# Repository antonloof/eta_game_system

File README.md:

# Eta game system
Playing games on a wall of TLS3001. Driven by a raspberry pi pico

## important docs
https://github.com/FastLED/FastLED/issues/1

Summary:
Manchester encoded data:
1 => 10
0 => 01
Timing is critical, keep constant period!
When sleeping put data low!

Sync frame: "1"*15+"0001"+"0"*11
(111111111111111000100000000000)

Reset frame: "1"*15 + "0100"
(1111111111111110100)

Data frame header: "1"*15 + "0010" 
(1111111111111110010)

Data content: "0"+"x"*12 + "0"+"x"*12 + "0"+"x"*12
where x is the rgb data to send total 39 bits per led
repeat this for all leds in series

The source:
Data communication protocol: 

Gave SDI input signal pin must follow the following definitions:

a. valid input data must be Manchester encoded signal. 

(from high to low transition indicates "1", from low to high Jump indicates "0")

b. During chip power after a synchronization frame must be sent to the chip detection of communication baud rate. Sync frame

Format is: 15'b111111111111111 + 4' b0001 +11' b00000000000, sending synchronization

Frame must be delayed for some time and then send the data frame, so that each chip can be done in order to accurately detect

To the communication baud rate, delay time (us) greater than: Connection chip count ÷ communication baud rate (MHz) × 30

c. several frames in the transmission data, re-send a reset frame, wait 1ms later, send it again with the

Step frames for the chip to eliminate the accumulated error, reset frame format:

15'b111111111111111 +4' b0100

d. data frame format is: 15'b111111111111111 +4' b0010 (header) + first chip

39bit second chip 39bit data + data + ...... + n-th chip 39bit data

e. first chip is first received data chips, chip data format is: 1 'b0 (identification bits) + 12'

bxxxxxxxxxxxx (output port 1 data) + 1'b0 (flag) + 12'bxxxxxxxxxxxx (input

The port 2 data) + 1'b0 (flag) + 12'bxxxxxxxxxxxx (output port 3 data),

x is 1 or the 0

f. data is first sent MSB (most significant bit)

g. SDI input pin in the idle state, must remain low

h. the same frame data transmission process, must be sent contiguously, in the middle, without interruption, transmission frequency can not be Changed.

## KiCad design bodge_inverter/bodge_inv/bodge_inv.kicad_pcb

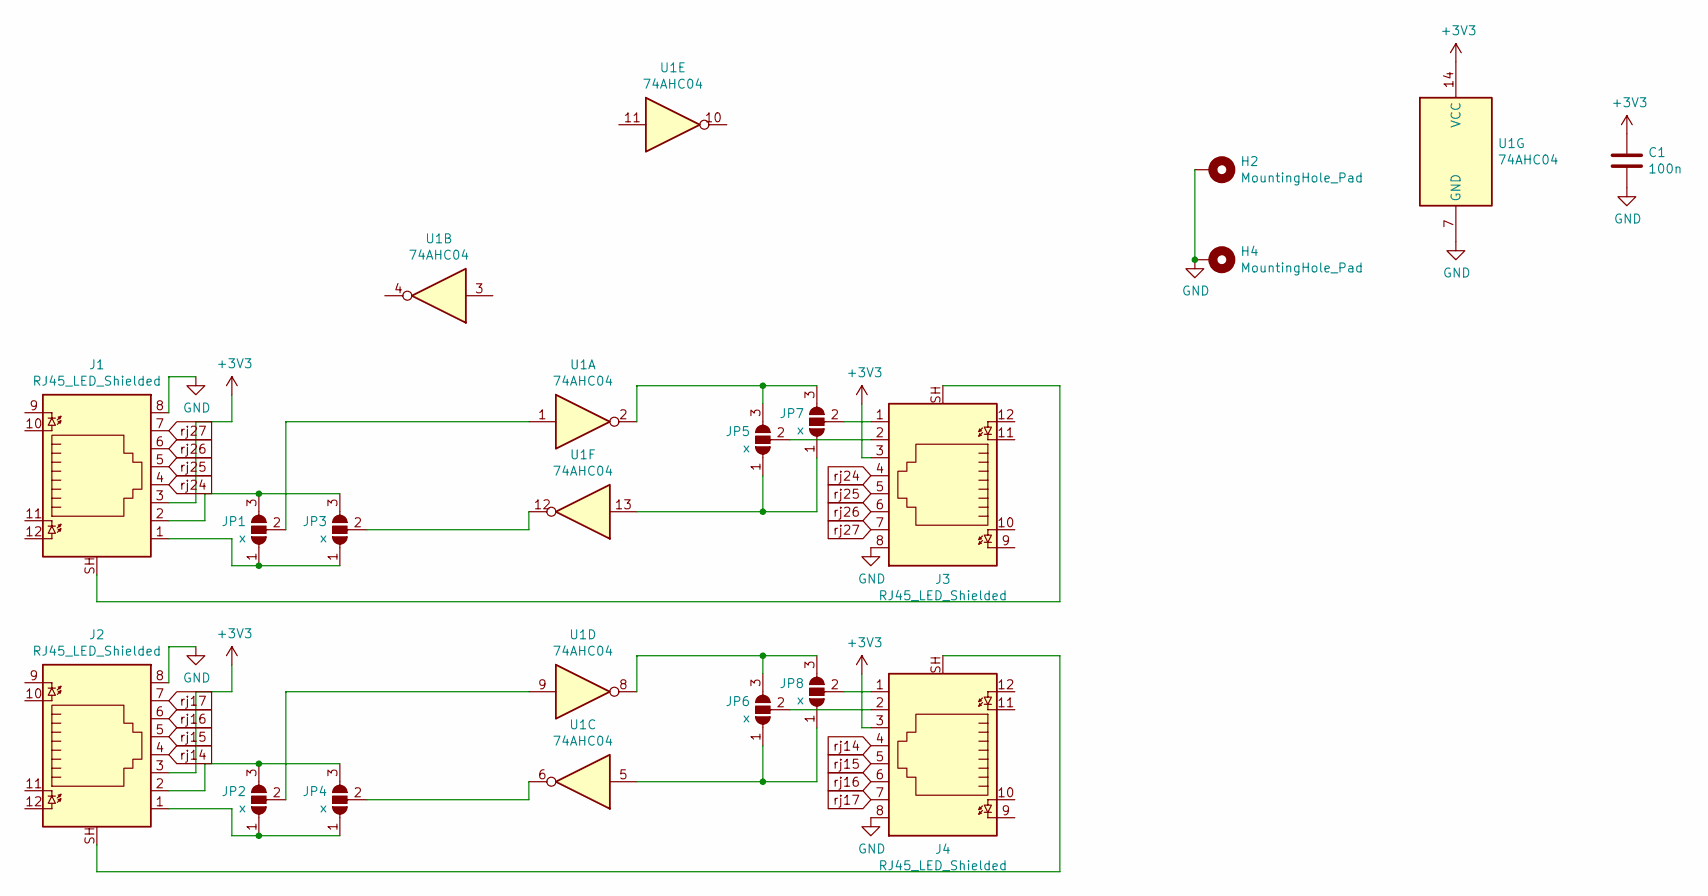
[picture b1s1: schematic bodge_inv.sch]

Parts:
C1: 100n; C_0603_1608Metric_Pad1.05x0.95mm_HandSolder
H2, H4: MountingHole_Pad; MountingHole_3.2mm_M3_Pad
J1, J2, J3, J4: RJ45_LED_Shielded; RJ45_BEL_SS74301-00x_Vertical
JP1, JP2, JP3, JP4, JP5, JP6, JP7, JP8: x; SolderJumper-3_P1.3mm_Open_Pad1.0x1.5mm_NumberLabels
U1: 74AHC04; SOIC-14_3.9x8.7mm_P1.27mm

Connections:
+3V3: C1.1, J1.3, J2.3, J3.3, J4.3, U1.14 (VCC)
GND: C1.2, H2.1, H4.1, J1.8, J2.8, J3.8, J4.8, U1.7 (GND)
unnamed: J1.1, JP1.1 (A), JP3.1 (A)
unnamed: J1.2, JP1.3 (B), JP3.3 (B)
unnamed: J1.SH, J3.SH
unnamed: J2.1, JP2.1 (A), JP4.1 (A)
unnamed: J2.2, JP2.3 (B), JP4.3 (B)
unnamed: J2.SH, J4.SH
unnamed: J3.1, JP7.2 (C)
unnamed: J3.2, JP5.2 (C)
unnamed: J4.1, JP8.2 (C)
unnamed: J4.2, JP6.2 (C)
unnamed: JP1.2 (C), U1.1
unnamed: JP2.2 (C), U1.9
unnamed: JP3.2 (C), U1.12
unnamed: JP4.2 (C), U1.6
unnamed: JP5.1 (A), JP7.1 (A), U1.13
unnamed: JP5.3 (B), JP7.3 (B), U1.2
unnamed: JP6.1 (A), JP8.1 (A), U1.5
unnamed: JP6.3 (B), JP8.3 (B), U1.8
rj14: J2.4, J4.4
rj15: J2.5, J4.5
rj16: J2.6, J4.6
rj17: J2.7, J4.7
rj24: J1.4, J3.4
rj25: J1.5, J3.5
rj26: J1.6, J3.6
rj27: J1.7, J3.7

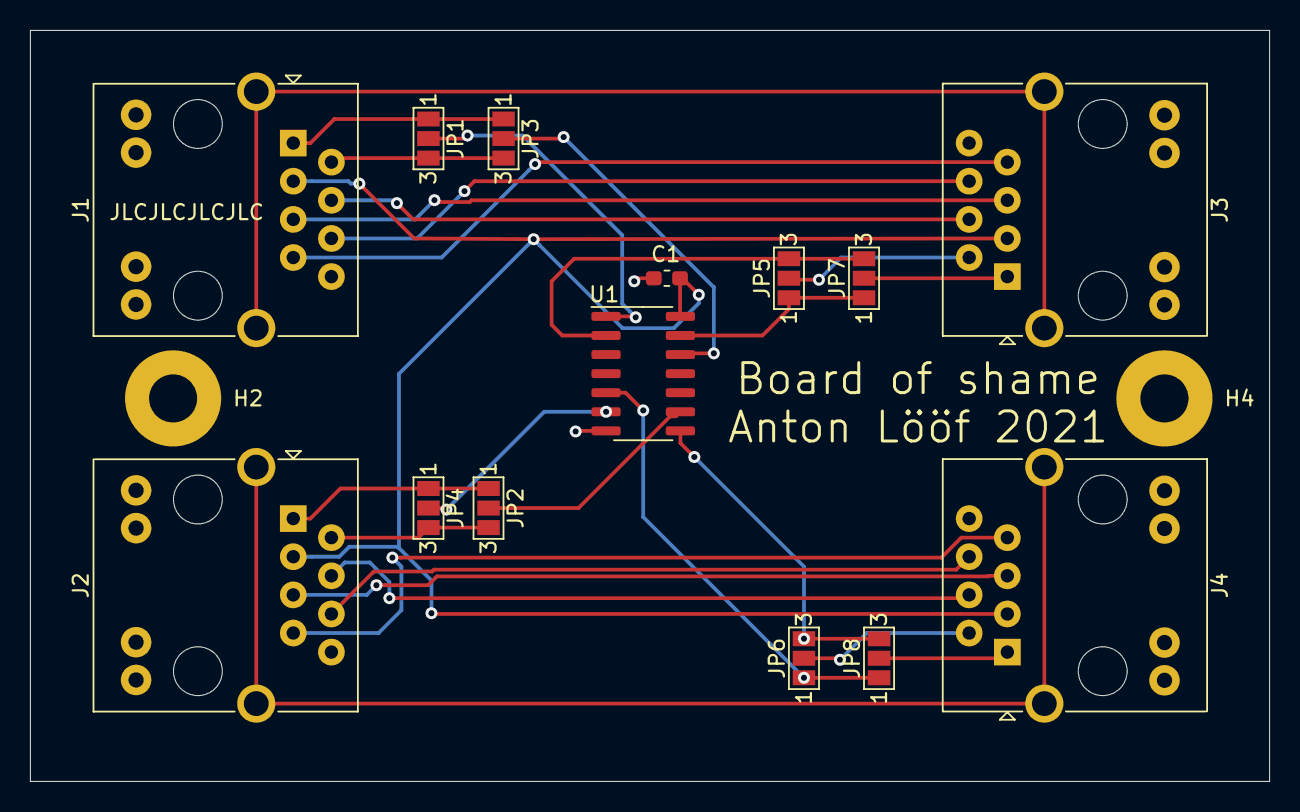
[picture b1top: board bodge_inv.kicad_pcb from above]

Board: 2 copper layers, 82.5 x 50.0 mm, 16 parts (0 on the bottom side), 28 nets.

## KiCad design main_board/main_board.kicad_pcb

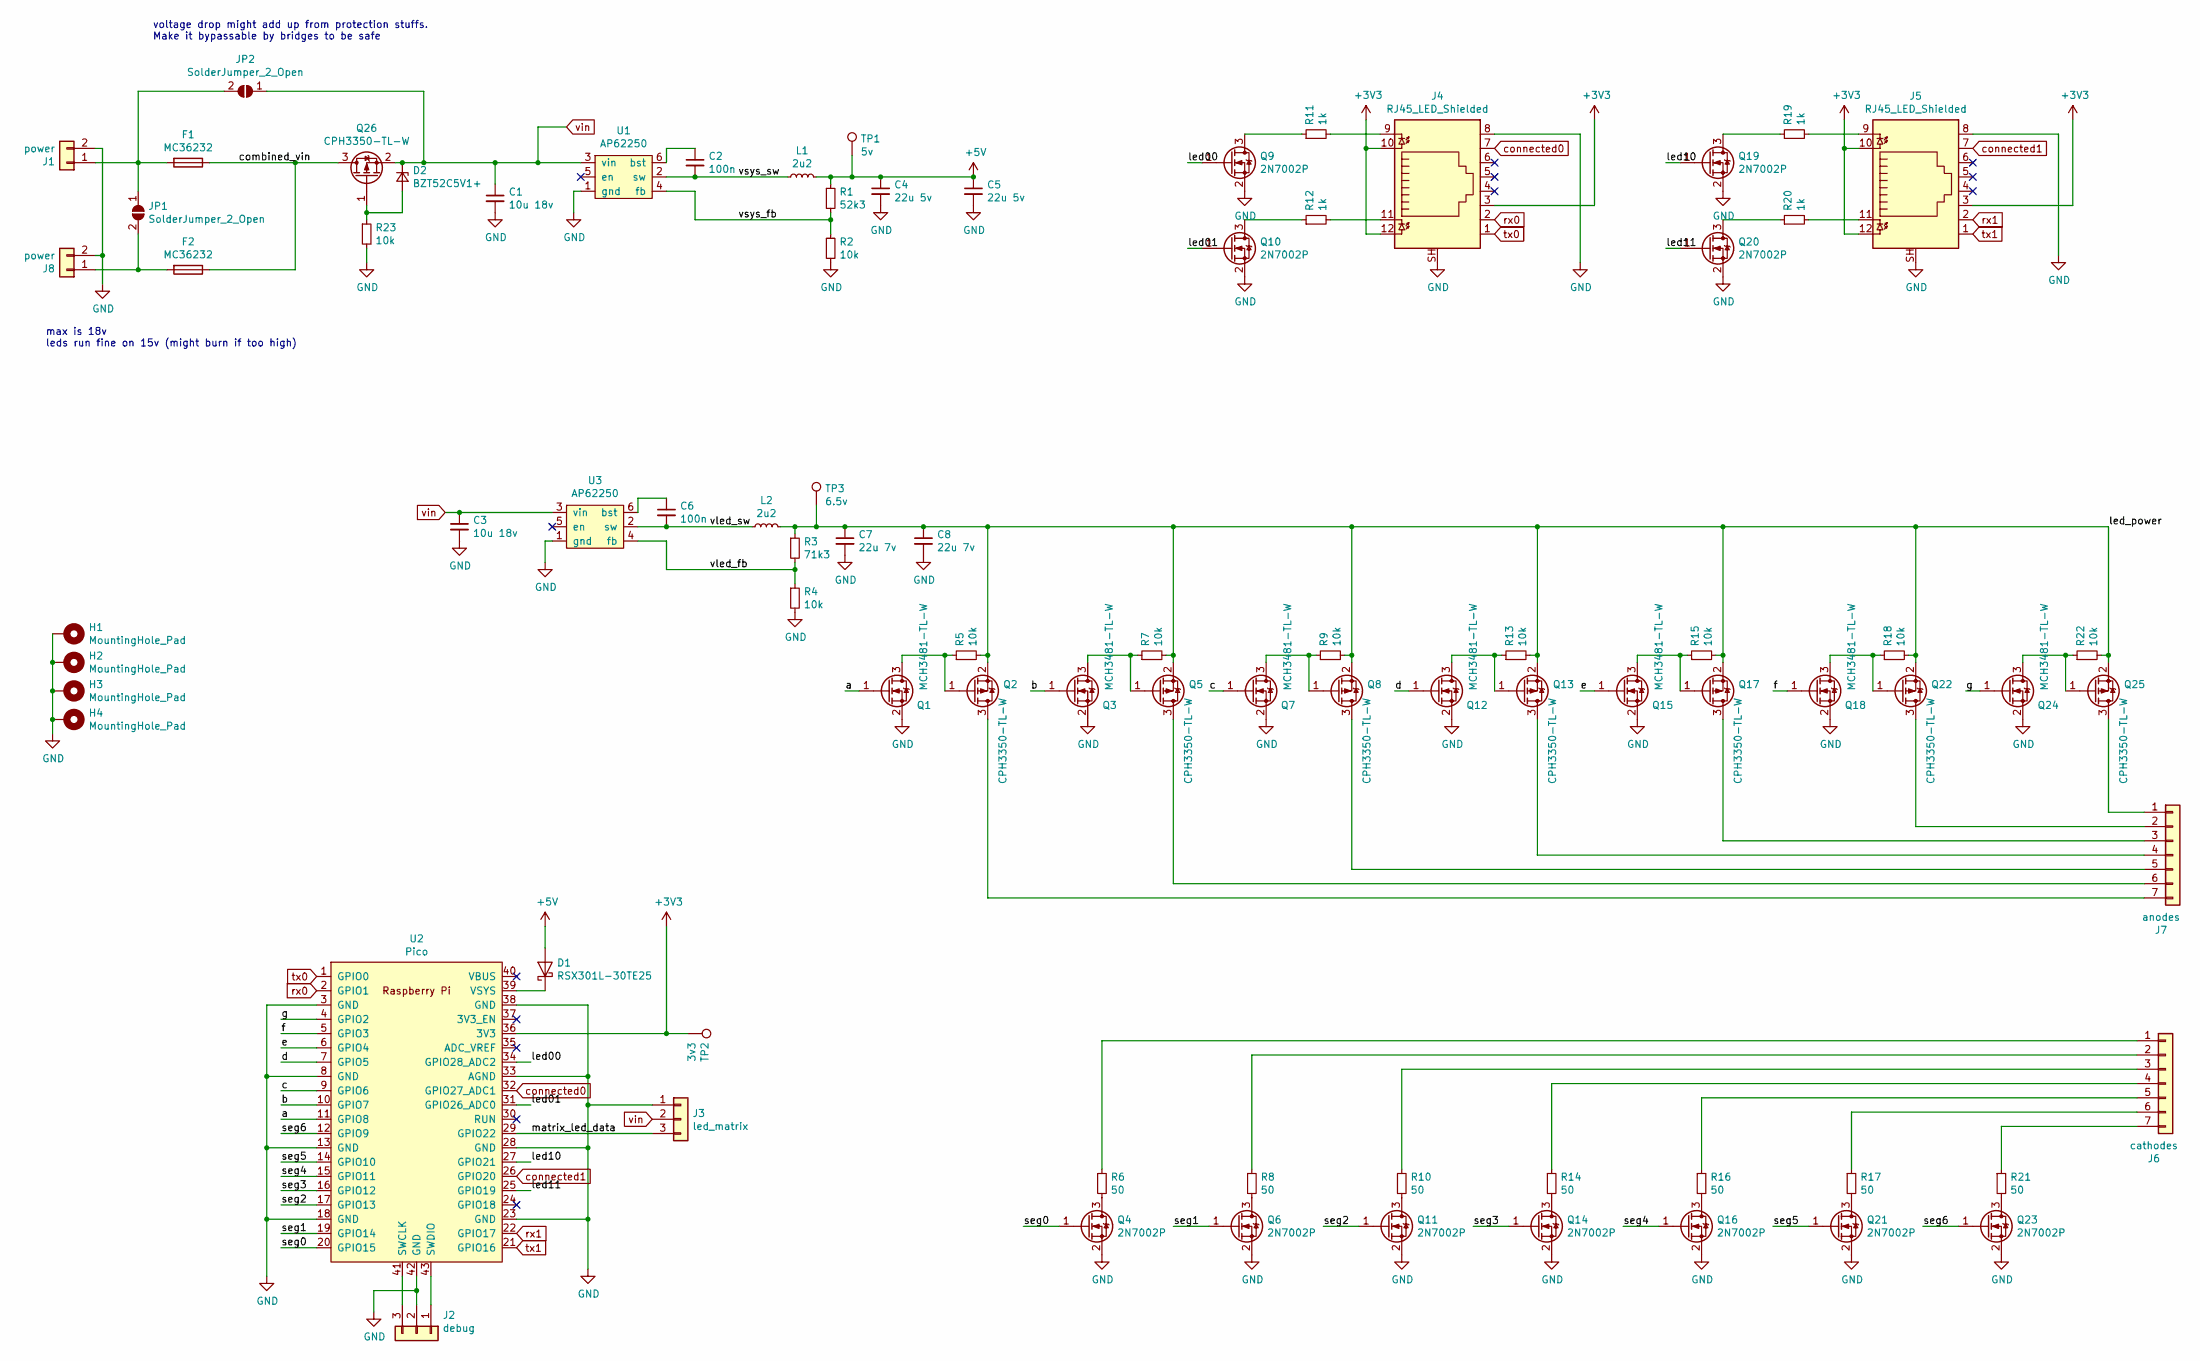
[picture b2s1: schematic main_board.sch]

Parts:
C1, C3: 10u 18v; C_1206_3216Metric
C2, C6: 100n; C_0603_1608Metric_Pad1.08x0.95mm_HandSolder
C4, C5: 22u 5v; C_0603_1608Metric_Pad1.08x0.95mm_HandSolder
C7, C8: 22u 7v; C_0805_2012Metric_Pad1.18x1.45mm_HandSolder
D1: RSX301L-30TE25; smd_diode_sod_106
D2: BZT52C5V1+; D_SOD-123
F1, F2: MC36232; Fuse_1812_4532Metric_Castellated
H1, H2, H3, H4: MountingHole_Pad; MountingHole_3.2mm_M3_Pad_TopBottom
J1, J8: power; TerminalBlock_Phoenix_MKDS-1,5-2_1x02_P5.00mm_Horizontal
J2: debug; PinHeader_1x03_P2.54mm_Vertical
J3: led_matrix; TerminalBlock_Phoenix_MKDS-1,5-3_1x03_P5.00mm_Horizontal
J4, J5: RJ45_LED_Shielded; RJ45_BEL_SS74301-00x_Vertical
J6: cathodes; PinHeader_1x07_P2.54mm_Vertical
J7: anodes; PinHeader_1x07_P2.54mm_Vertical
JP1, JP2: SolderJumper_2_Open; SolderJumper-2_P1.3mm_Open_TrianglePad1.0x1.5mm
L1, L2: 2u2; smd_inductor_0806_2016metric
Q1, Q3, Q7, Q12, Q15, Q18, Q24: MCH3481-TL-W; SOT-323_SC-70_Handsoldering
Q2, Q5, Q8, Q13, Q17, Q22, Q25, Q26: CPH3350-TL-W; SOT-23_Handsoldering
Q4, Q6, Q9, Q10, Q11, Q14, Q16, Q19, Q20, Q21, Q23: 2N7002P; SOT-23_Handsoldering
R1: 52k3; R_0603_1608Metric_Pad0.98x0.95mm_HandSolder
R2, R4, R5, R7, R9, R13, R15, R18, R22, R23: 10k; R_0603_1608Metric_Pad0.98x0.95mm_HandSolder
R3: 71k3; R_0603_1608Metric_Pad0.98x0.95mm_HandSolder
R6, R8, R10, R14, R16, R17, R21: 50; R_0603_1608Metric_Pad0.98x0.95mm_HandSolder
R11, R12, R19, R20: 1k; R_0603_1608Metric_Pad0.98x0.95mm_HandSolder
TP1: 5v; TestPoint_Pad_D1.5mm
TP2: 3v3; TestPoint_Pad_D1.5mm
TP3: 6.5v; TestPoint_Pad_D1.5mm
U1, U3: AP62250; TSOT-23-6
U2: Pico; RPi_Pico_SMD_TH

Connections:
+3V3: J4.3, J4.10, J4.12, J5.3, J5.10, J5.12, TP2.1, U2.36 (3V3)
+5V: C4.1, C5.1, D1.2 (A), L1.2, R1.1, TP1.1
/a: Q1.1 (G), U2.11 (GPIO8)
/b: Q3.1 (G), U2.10 (GPIO7)
/c: Q7.1 (G), U2.9 (GPIO6)
/combined_vin: F1.1, F2.1, Q26.3 (D)
/d: Q12.1 (G), U2.7 (GPIO5)
/e: Q15.1 (G), U2.6 (GPIO4)
/f: Q18.1 (G), U2.5 (GPIO3)
/g: Q24.1 (G), U2.4 (GPIO2)
/led00: Q9.1 (G), U2.34 (GPIO28_ADC2)
/led01: Q10.1 (G), U2.31 (GPIO26_ADC0)
/led10: Q19.1 (G), U2.27 (GPIO21)
/led11: Q20.1 (G), U2.25 (GPIO19)
/led_power: C7.1, C8.1, L2.2, Q2.2 (S), Q5.2 (S), Q8.2 (S), Q13.2 (S), Q17.2 (S), Q22.2 (S), Q25.2 (S), R3.1, R5.2, R7.2, R9.2, R13.2, R15.2, R18.2, R22.2, TP3.1
/matrix_led_data: J3.3, U2.29 (GPIO22)
/seg0: Q4.1 (G), U2.20 (GPIO15)
/seg1: Q6.1 (G), U2.19 (GPIO14)
/seg2: Q11.1 (G), U2.17 (GPIO13)
/seg3: Q14.1 (G), U2.16 (GPIO12)
/seg4: Q16.1 (G), U2.15 (GPIO11)
/seg5: Q21.1 (G), U2.14 (GPIO10)
/seg6: Q23.1 (G), U2.12 (GPIO9)
/vled_fb: R3.2, R4.1, U3.4 (fb)
/vled_sw: C6.2, L2.1, U3.2 (sw)
/vsys_fb: R1.2, R2.1, U1.4 (fb)
/vsys_sw: C2.2, L1.1, U1.2 (sw)
GND: C1.2, C3.2, C4.2, C5.2, C7.2, C8.2, H1.1, H2.1, H3.1, H4.1, J1.2, J2.2, J3.1, J4.8, J4.SH, J5.8, J5.SH, J8.2, Q1.2 (S), Q3.2 (S), Q4.2 (S), Q6.2 (S), Q7.2 (S), Q9.2 (S), Q10.2 (S), Q11.2 (S), Q12.2 (S), Q14.2 (S), Q15.2 (S), Q16.2 (S), Q18.2 (S), Q19.2 (S), Q20.2 (S), Q21.2 (S), Q23.2 (S), Q24.2 (S), R2.2, R4.2, R23.2, U1.1 (gnd), U2.3 (GND), U2.8 (GND), U2.13 (GND), U2.18 (GND), U2.23 (GND), U2.28 (GND), U2.33 (AGND), U2.38 (GND), U2.42 (GND), U3.1 (gnd)
unnamed: C2.1, U1.6 (bst)
unnamed: C6.1, U3.6 (bst)
unnamed: D1.1 (K), U2.39 (VSYS)
unnamed: D2.2 (A), Q26.1 (G), R23.1
unnamed: F1.2, J1.1, JP1.1 (A), JP2.2 (B)
unnamed: F2.2, J8.1, JP1.2 (B)
unnamed: J2.1, U2.43 (SWDIO)
unnamed: J2.3, U2.41 (SWCLK)
unnamed: J4.9, R11.2
unnamed: J4.11, R12.2
unnamed: J5.9, R19.2
unnamed: J5.11, R20.2
unnamed: J6.1, R6.1
unnamed: J6.2, R8.1
unnamed: J6.3, R10.1
unnamed: J6.4, R14.1
unnamed: J6.5, R16.1
unnamed: J6.6, R17.1
unnamed: J6.7, R21.1
unnamed: J7.1, Q25.3 (D)
unnamed: J7.2, Q22.3 (D)
unnamed: J7.3, Q17.3 (D)
unnamed: J7.4, Q13.3 (D)
unnamed: J7.5, Q8.3 (D)
unnamed: J7.6, Q5.3 (D)
unnamed: J7.7, Q2.3 (D)
unnamed: Q1.3 (D), Q2.1 (G), R5.1
unnamed: Q3.3 (D), Q5.1 (G), R7.1
unnamed: Q4.3 (D), R6.2
unnamed: Q6.3 (D), R8.2
unnamed: Q7.3 (D), Q8.1 (G), R9.1
unnamed: Q9.3 (D), R11.1
unnamed: Q10.3 (D), R12.1
unnamed: Q11.3 (D), R10.2
unnamed: Q12.3 (D), Q13.1 (G), R13.1
unnamed: Q14.3 (D), R14.2
unnamed: Q15.3 (D), Q17.1 (G), R15.1
unnamed: Q16.3 (D), R16.2
unnamed: Q18.3 (D), Q22.1 (G), R18.1
unnamed: Q19.3 (D), R19.1
unnamed: Q20.3 (D), R20.1
unnamed: Q21.3 (D), R17.2
unnamed: Q23.3 (D), R21.2
unnamed: Q24.3 (D), Q25.1 (G), R22.1
connected0: J4.7, U2.32 (GPIO27_ADC1)
connected1: J5.7, U2.26 (GPIO20)
rx0: J4.2, U2.2 (GPIO1)
rx1: J5.2, U2.22 (GPIO17)
tx0: J4.1, U2.1 (GPIO0)
tx1: J5.1, U2.21 (GPIO16)
vin: C1.1, C3.1, D2.1 (K), J3.2, JP2.1 (A), Q26.2 (S), U1.3 (vin), U3.3 (vin)

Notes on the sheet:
max is 18v leds run fine on 15v (might burn if too high)
voltage drop might add up from protection stuffs. Make it bypassable by bridges to be safe

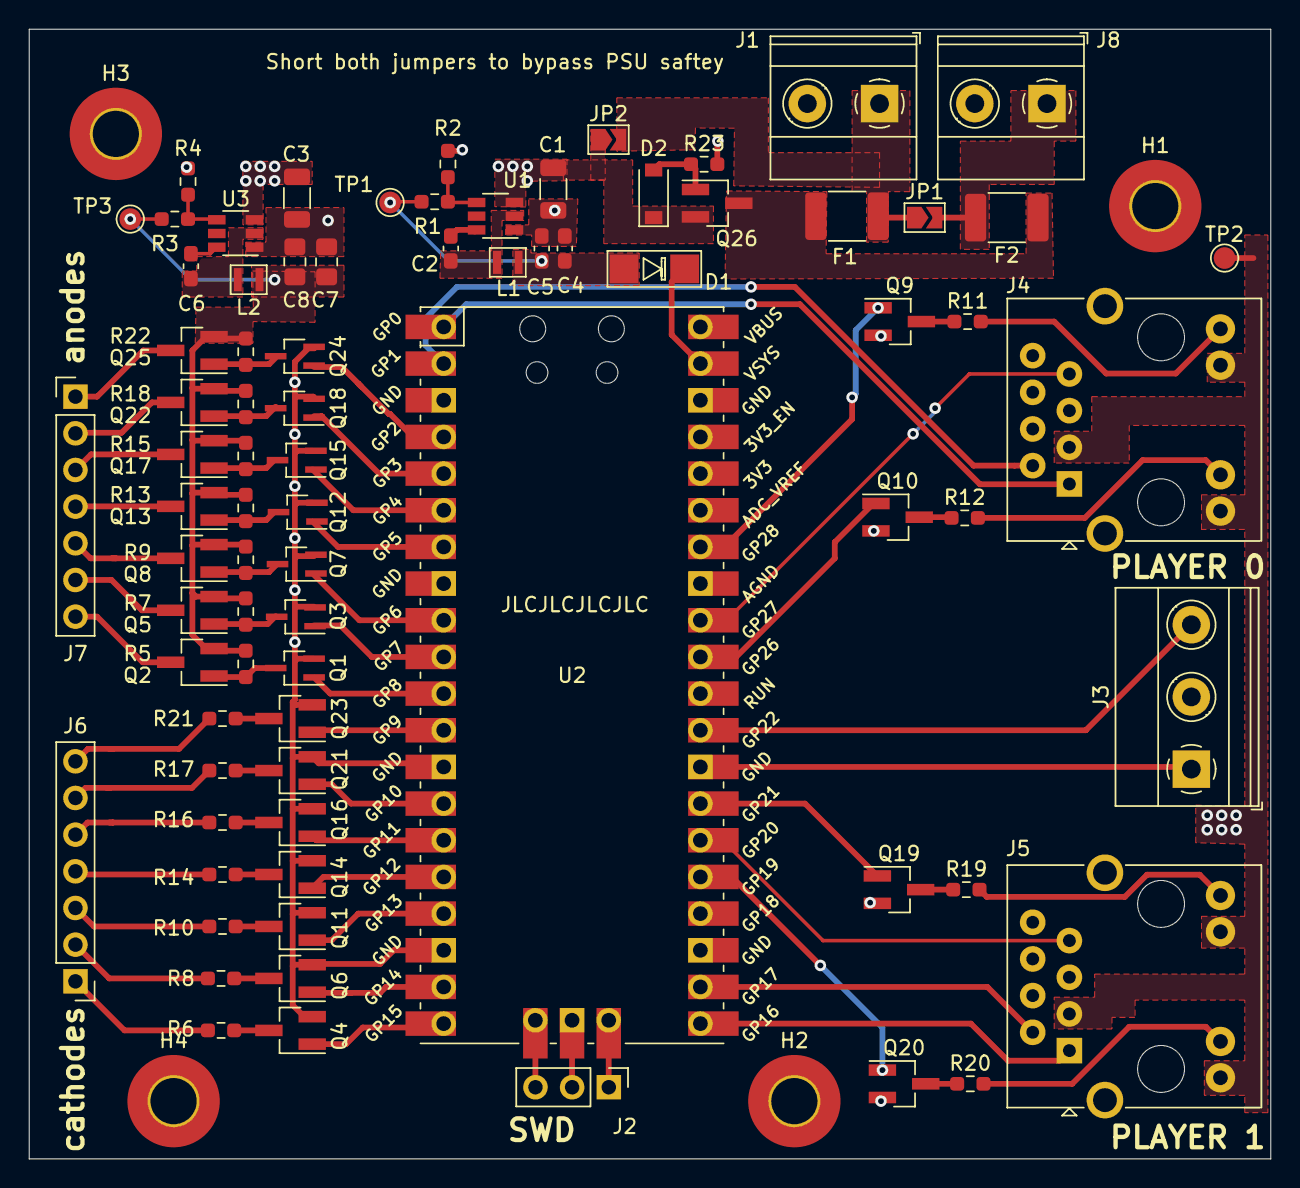
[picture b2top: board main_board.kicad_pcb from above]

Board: 2 copper layers, 86.0 x 78.2 mm, 83 parts (0 on the bottom side), 79 nets.

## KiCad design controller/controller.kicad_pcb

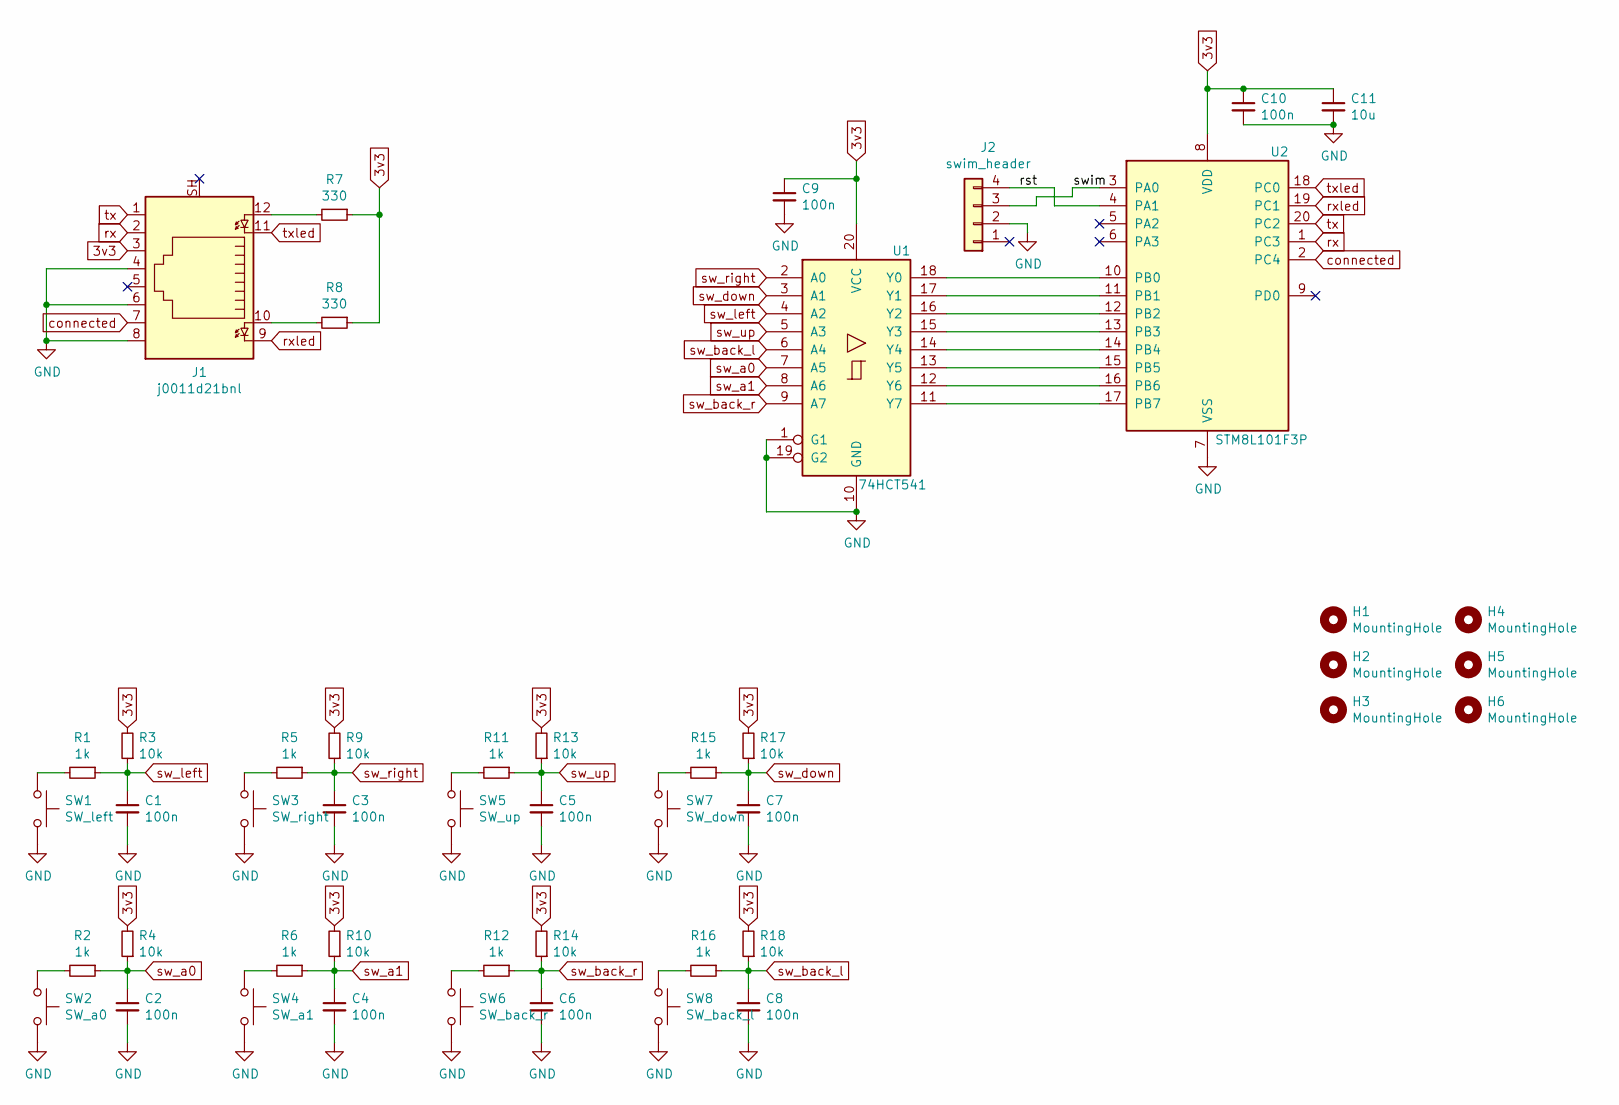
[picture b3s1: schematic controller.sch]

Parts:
C1, C2, C3, C4, C5, C6, C7, C8, C9, C10: 100n; C_0603_1608Metric_Pad1.08x0.95mm_HandSolder
C11: 10u; C_0603_1608Metric_Pad1.08x0.95mm_HandSolder
H1, H2, H3, H4, H5, H6: MountingHole; MountingHole_3.2mm_M3
J1: j0011d21bnl; RJ45_BEL_SS74301-00x_Vertical
J2: swim_header; TSM-104-01-L-SH
R1, R2, R5, R6, R11, R12, R15, R16: 1k; R_0603_1608Metric_Pad0.98x0.95mm_HandSolder
R3, R4, R9, R10, R13, R14, R17, R18: 10k; R_0603_1608Metric_Pad0.98x0.95mm_HandSolder
R7, R8: 330; R_0603_1608Metric_Pad0.98x0.95mm_HandSolder
SW1: SW_left; SW_Cherry_MX_1.00u_Plate
SW2: SW_a0; SW_Cherry_MX_1.00u_Plate
SW3: SW_right; SW_Cherry_MX_1.00u_Plate
SW4: SW_a1; SW_Cherry_MX_1.00u_Plate
SW5: SW_up; SW_Cherry_MX_1.00u_Plate
SW6: SW_back_r; TSM-102-01-l_SH
SW7: SW_down; SW_Cherry_MX_1.00u_Plate
SW8: SW_back_l; TSM-102-01-l_SH
U1: 74HCT541; TSSOP-20_4.4x6.5mm_P0.65mm
U2: STM8L101F3P; TSSOP-20_4.4x6.5mm_P0.65mm

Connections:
3v3: C9.1, C10.1, C11.1, J1.3, R3.2, R4.2, R7.1, R8.1, R9.2, R10.2, R13.2, R14.2, R17.2, R18.2, U1.20 (VCC), U2.8 (VDD)
/rst: J2.4, U2.4 (PA1)
/swim: J2.3, U2.3 (PA0)
GND: C1.2, C2.2, C3.2, C4.2, C5.2, C6.2, C7.2, C8.2, C9.2, C10.2, C11.2, J1.4, J1.6, J1.8, J2.2, SW1.2, SW2.2, SW3.2, SW4.2, SW5.2, SW6.2, SW7.2, SW8.2, U1.1 (G1), U1.10 (GND), U1.19 (G2), U2.7 (VSS)
unnamed: J1.10, R8.2
unnamed: J1.12, R7.2
unnamed: R1.2, SW1.1
unnamed: R2.2, SW2.1
unnamed: R5.2, SW3.1
unnamed: R6.2, SW4.1
unnamed: R11.2, SW5.1
unnamed: R12.2, SW6.1
unnamed: R15.2, SW7.1
unnamed: R16.2, SW8.1
unnamed: U1.11 (Y7), U2.17 (PB7)
unnamed: U1.12 (Y6), U2.16 (PB6)
unnamed: U1.13 (Y5), U2.15 (PB5)
unnamed: U1.14 (Y4), U2.14 (PB4)
unnamed: U1.15 (Y3), U2.13 (PB3)
unnamed: U1.16 (Y2), U2.12 (PB2)
unnamed: U1.17 (Y1), U2.11 (PB1)
unnamed: U1.18 (Y0), U2.10 (PB0)
connected: J1.7, U2.2 (PC4)
rx: J1.2, U2.1 (PC3)
rxled: J1.9, U2.19 (PC1)
sw_a0: C2.1, R2.1, R4.1, U1.7 (A5)
sw_a1: C4.1, R6.1, R10.1, U1.8 (A6)
sw_back_l: C8.1, R16.1, R18.1, U1.6 (A4)
sw_back_r: C6.1, R12.1, R14.1, U1.9 (A7)
sw_down: C7.1, R15.1, R17.1, U1.3 (A1)
sw_left: C1.1, R1.1, R3.1, U1.4 (A2)
sw_right: C3.1, R5.1, R9.1, U1.2 (A0)
sw_up: C5.1, R11.1, R13.1, U1.5 (A3)
tx: J1.1, U2.20 (PC2)
txled: J1.11, U2.18 (PC0)

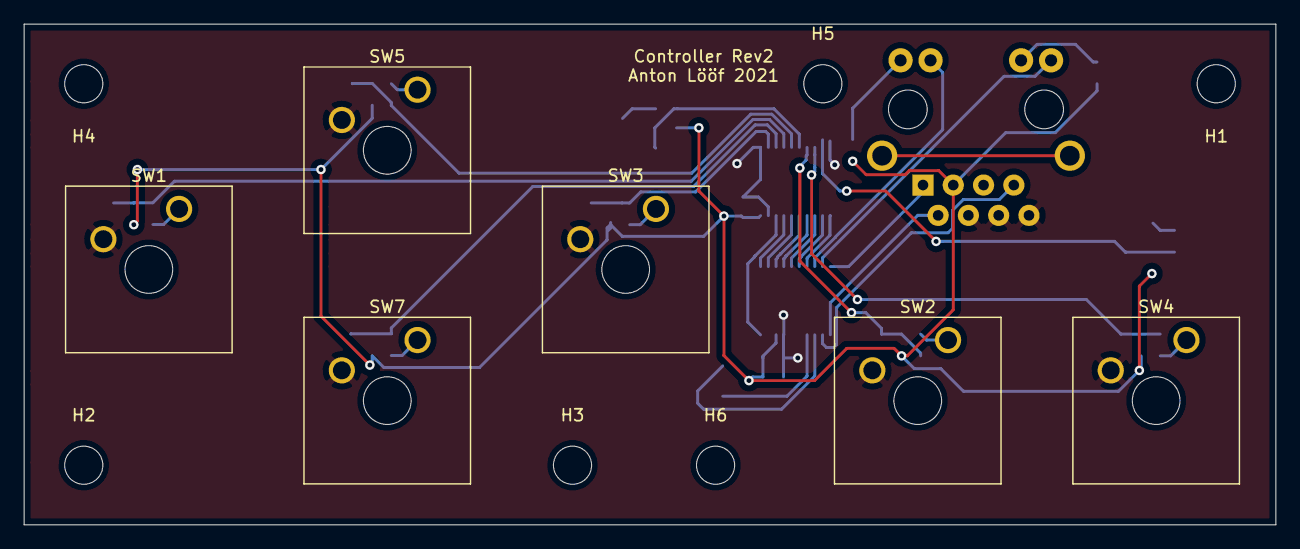
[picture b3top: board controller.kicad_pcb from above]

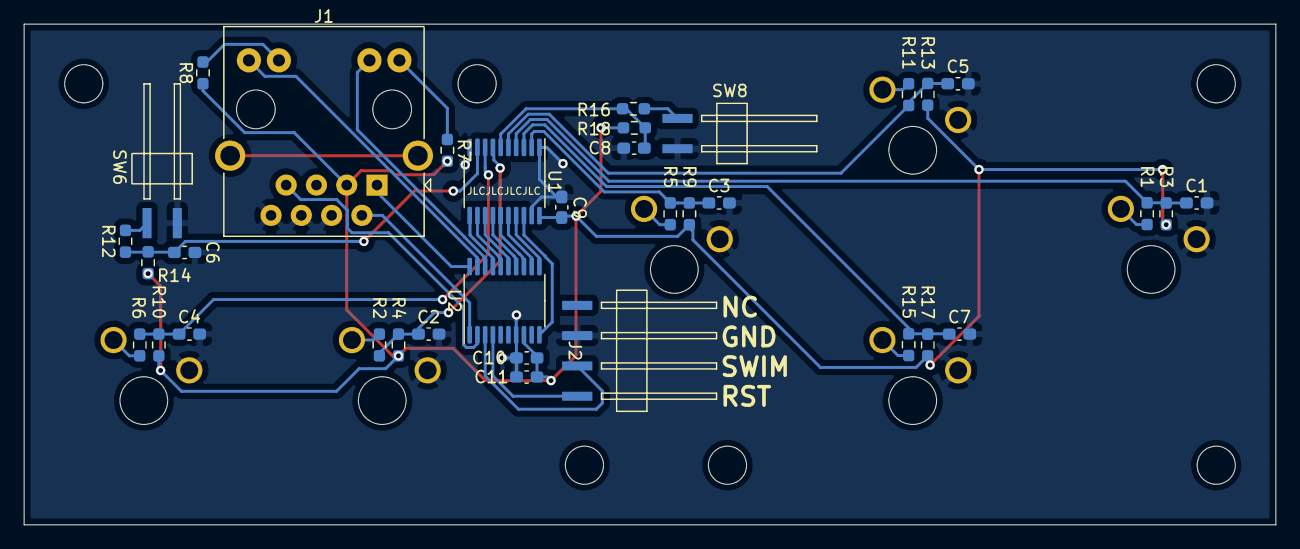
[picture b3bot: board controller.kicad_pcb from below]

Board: 2 copper layers, 105.0 x 42.0 mm, 47 parts (35 on the bottom side), 35 nets.

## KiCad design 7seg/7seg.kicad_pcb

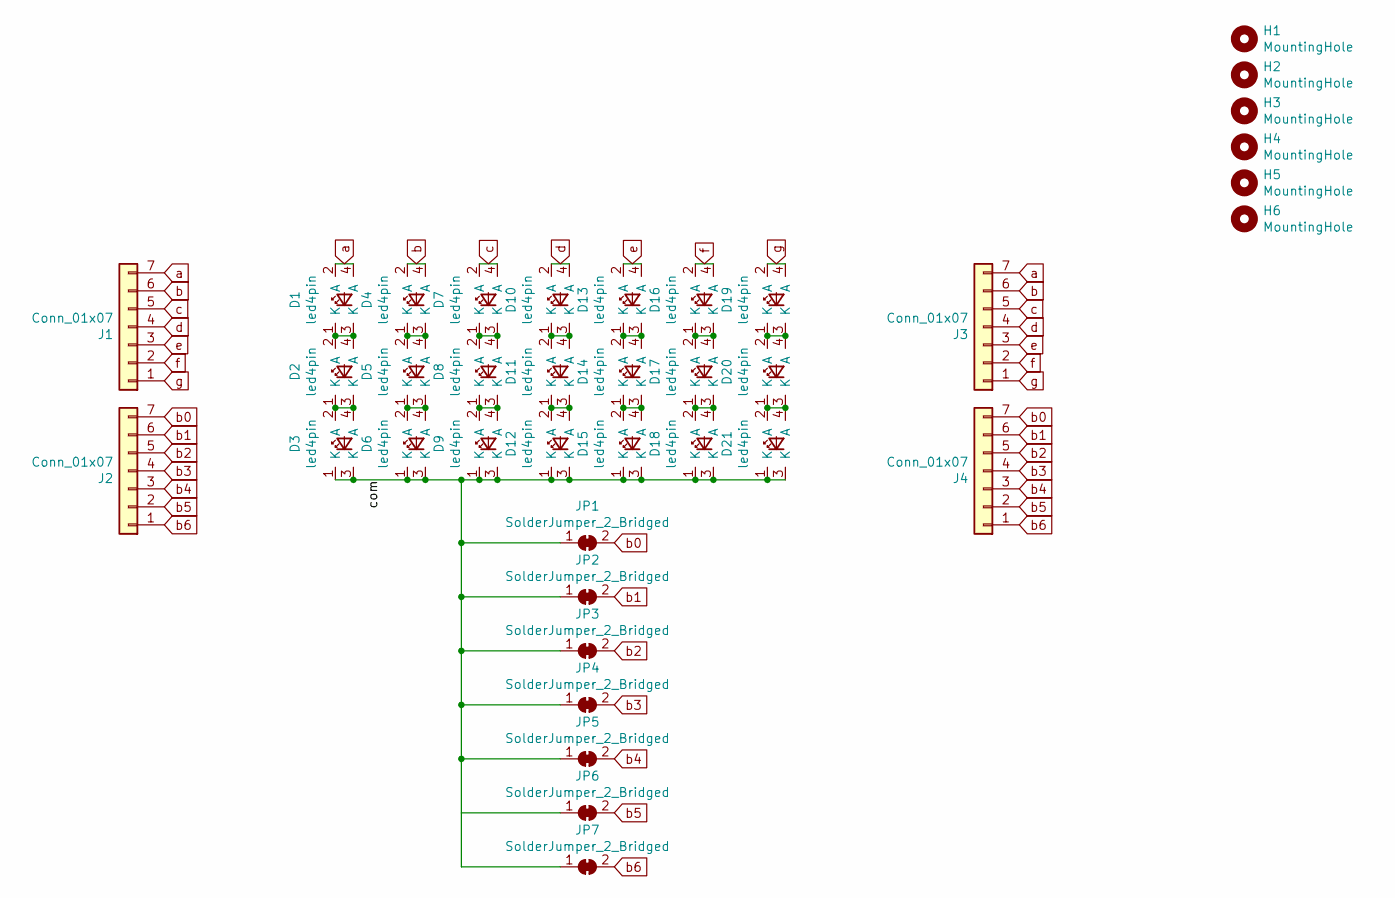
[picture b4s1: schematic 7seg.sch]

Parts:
D1, D2, D3, D4, D5, D6, D7, D8, D9, D10, D11, D12, D13, D14, D15, D16, D17, D18, D19, D20, D21: led4pin
H1, H2, H3, H4, H5, H6: MountingHole; MountingHole_3.2mm_M3
J1, J2: Conn_01x07; pin-socket-7x2.54
J3, J4: Conn_01x07; PinHeader_1x07_P2.54mm_Horizontal
JP1, JP2, JP3, JP4, JP5, JP6, JP7: SolderJumper_2_Bridged; SolderJumper-2_P1.3mm_Open_TrianglePad1.0x1.5mm

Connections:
/com: D3.1 (K), D3.3 (K), D6.1 (K), D6.3 (K), D9.1 (K), D9.3 (K), D12.1 (K), D12.3 (K), D15.1 (K), D15.3 (K), D18.1 (K), D18.3 (K), D21.1 (K), D21.3 (K), JP1.1 (A), JP2.1 (A), JP3.1 (A), JP4.1 (A), JP5.1 (A), JP6.1 (A), JP7.1 (A)
unnamed: D1.1 (K), D1.3 (K), D2.2 (A), D2.4 (A)
unnamed: D2.1 (K), D2.3 (K), D3.2 (A), D3.4 (A)
unnamed: D4.1 (K), D4.3 (K), D5.2 (A), D5.4 (A)
unnamed: D5.1 (K), D5.3 (K), D6.2 (A), D6.4 (A)
unnamed: D7.1 (K), D7.3 (K), D8.2 (A), D8.4 (A)
unnamed: D8.1 (K), D8.3 (K), D9.2 (A), D9.4 (A)
unnamed: D10.1 (K), D10.3 (K), D11.2 (A), D11.4 (A)
unnamed: D11.1 (K), D11.3 (K), D12.2 (A), D12.4 (A)
unnamed: D13.1 (K), D13.3 (K), D14.2 (A), D14.4 (A)
unnamed: D14.1 (K), D14.3 (K), D15.2 (A), D15.4 (A)
unnamed: D16.1 (K), D16.3 (K), D17.2 (A), D17.4 (A)
unnamed: D17.1 (K), D17.3 (K), D18.2 (A), D18.4 (A)
unnamed: D19.1 (K), D19.3 (K), D20.2 (A), D20.4 (A)
unnamed: D20.1 (K), D20.3 (K), D21.2 (A), D21.4 (A)
a: D1.2 (A), D1.4 (A), J1.7, J3.7
b: D4.2 (A), D4.4 (A), J1.6, J3.6
b0: J2.7, J4.7, JP1.2 (B)
b1: J2.6, J4.6, JP2.2 (B)
b2: J2.5, J4.5, JP3.2 (B)
b3: J2.4, J4.4, JP4.2 (B)
b4: J2.3, J4.3, JP5.2 (B)
b5: J2.2, J4.2, JP6.2 (B)
b6: J2.1, J4.1, JP7.2 (B)
c: D7.2 (A), D7.4 (A), J1.5, J3.5
d: D10.2 (A), D10.4 (A), J1.4, J3.4
e: D13.2 (A), D13.4 (A), J1.3, J3.3
f: D16.2 (A), D16.4 (A), J1.2, J3.2
g: D19.2 (A), D19.4 (A), J1.1, J3.1

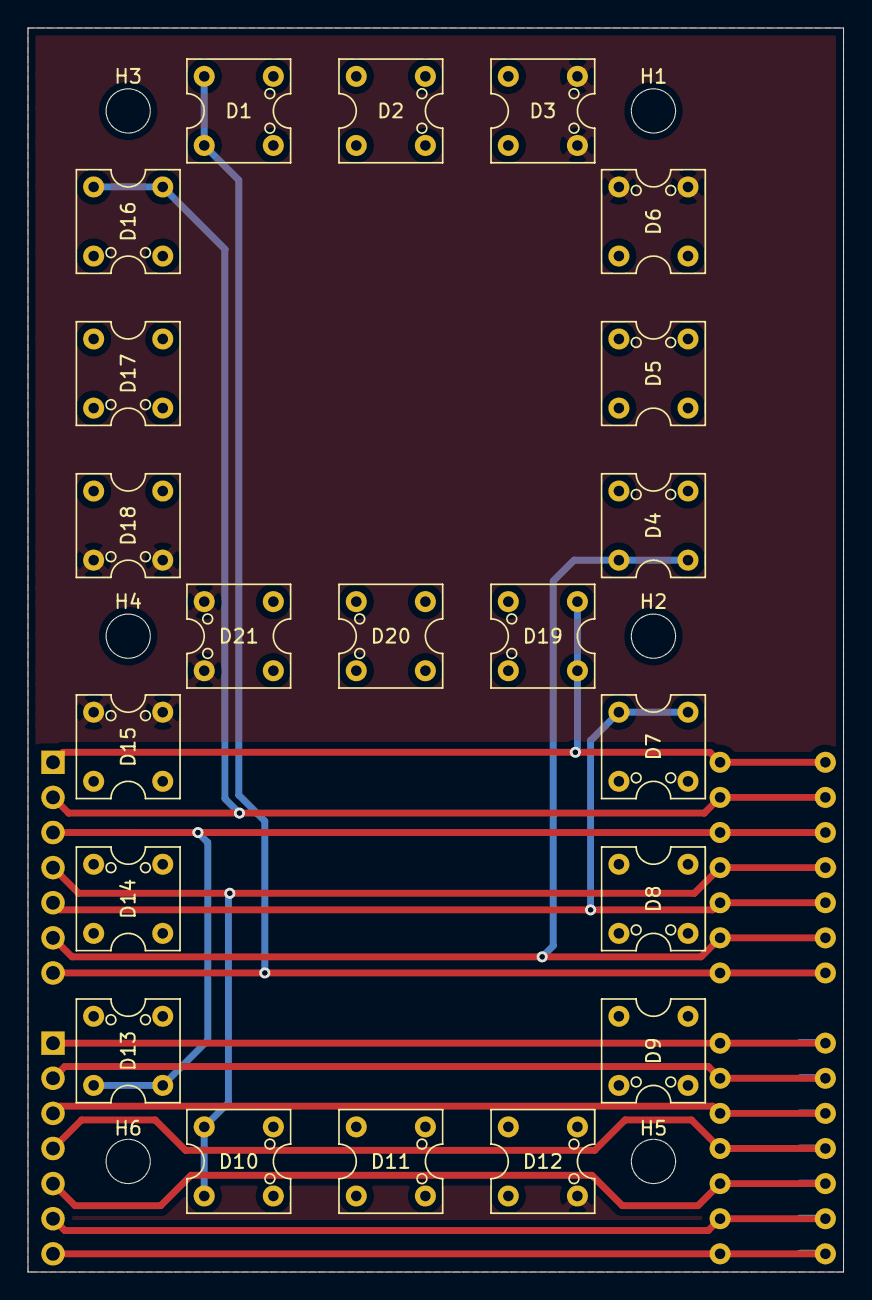
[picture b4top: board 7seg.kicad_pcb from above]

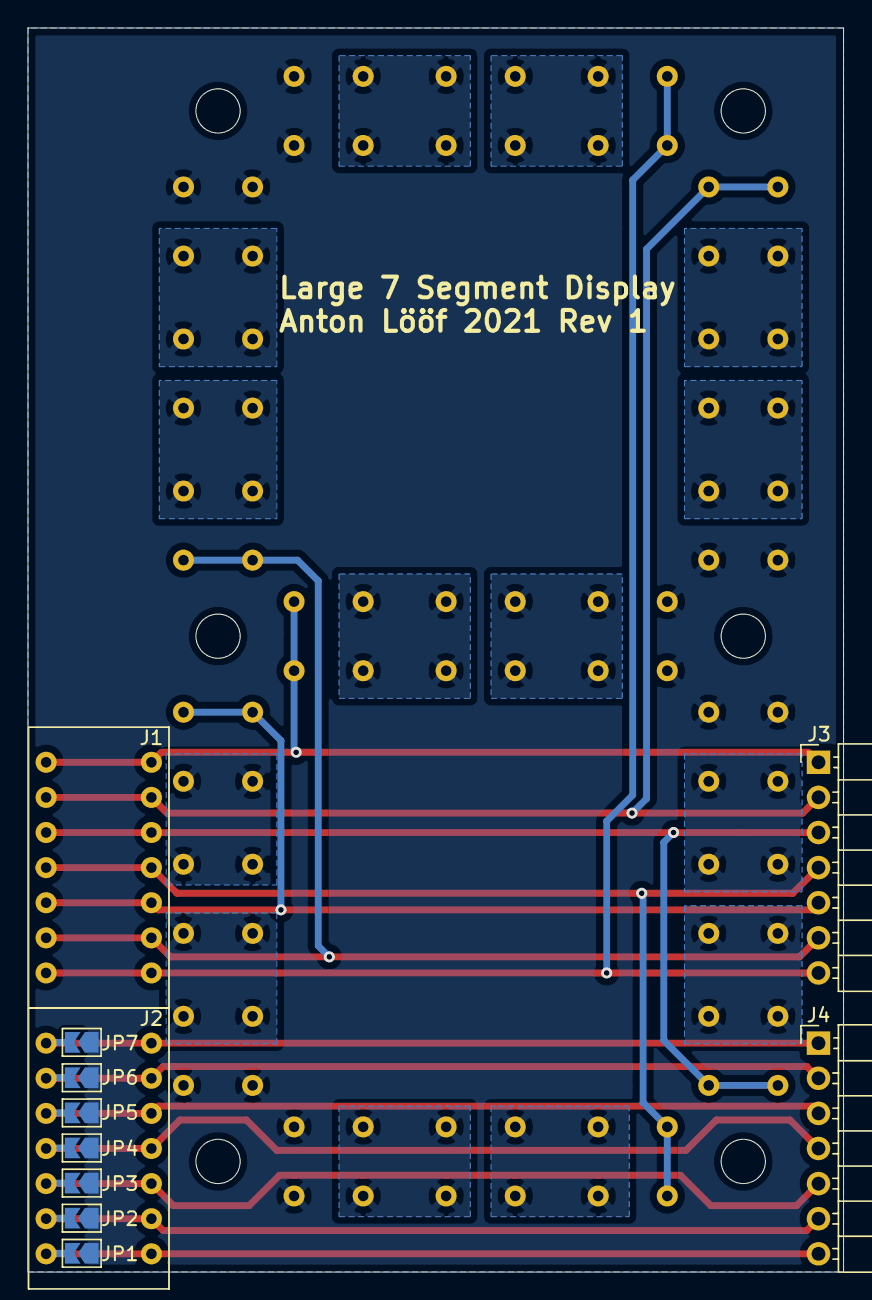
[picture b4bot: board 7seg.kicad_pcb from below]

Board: 2 copper layers, 59.0 x 90.0 mm, 38 parts (11 on the bottom side), 29 nets.

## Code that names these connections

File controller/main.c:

#include "stm8l101f3.h" 

#define DEBUONCE_THRESH 100

unsigned char received, last_received;

int count = 0;
int has_send = 1;

main()
{
	sfr_CLK.CKDIVR.byte = 0; // FULL SPEED
	sfr_CLK.PCKENR.byte = 0xFF; // enable all (usart)

	// PC0 and PC1 push pull for leds (does not work, are OD only)
	// PC4 should output a "high" all the time
	// PC3 is tx and should be output, push pull, high speed
	// PC2 is rx and should be input no interrupt
	sfr_PORTC.DDR.byte = 0b00011011;
	sfr_PORTC.CR1.C10 = 1; // push pull
	sfr_PORTC.CR1.C11 = 1; // push pull
	sfr_PORTC.CR1.C13 = 1; // push pull
	sfr_PORTC.CR1.C14 = 1; // push pull
	sfr_PORTC.CR2.C23 = 1; // high speed
	
	// port b is all inputs with pullups. 
	sfr_PORTB.DDR.byte = 0;
	sfr_PORTB.CR1.byte = 0xFF;
	sfr_PORTB.CR2.byte = 0;
	
	
	// configure usart
	sfr_USART.CR1.USARTD = 0; // dont disable
	sfr_USART.CR1.MSL = 0; // 8 bit bytes
	sfr_USART.CR3.STOP = 0; // 1 stop bit

	// baudrate 16Mhz/115200 baud ~= 139 = 0x008B
	// bbr2 should be written to first, update on brr1 write
	sfr_USART.BRR2.byte = 0x0B;
	sfr_USART.BRR1.byte = 0x08;
	
	sfr_USART.CR2.TEN = 1; // enable transmitter
	
	// the controller is connected
	sfr_PORTC.ODR.ODR4 = 1;
	
	last_received = sfr_PORTB.IDR.byte;
	while (1) {
		received = sfr_PORTB.IDR.byte;

		if (!has_send) {
			if (received == last_received) {
				count++;
				if (count == DEBUONCE_THRESH) {
					count = 0;
					has_send = 1;
					while (!sfr_USART.SR.TXE);
					sfr_USART.DR.byte = received;
				}
			} else {
				count = 0;
			}
		} else {
			if (received != last_received) {
				has_send = 0;
			}
		}
		last_received = received;
	}
}

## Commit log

2021-05-16 readme
2021-05-20 WURKS!!!
2021-05-22 Work around with DMA
2021-05-26 Now with 100% more dma blinking
2021-05-28 Hey oh it works
2021-06-01 Tetris now up and running
2021-06-01 Add 7seg display pcb
2021-06-02 rev 1 of 7seg
2021-07-18 Add controller pcb rev1
2021-07-19 Remove bs file
2021-08-08 Now with extra leds for secondary screens
2021-08-08 Update footprint for controller buffer
2021-08-09 now without speakers now with fets for 7seg
2021-08-10 Finalize schematic
2021-08-14 Refactor TLS3001 ctrl
2021-08-14 Move extra leds logic to own files
    also make secondary displays "work" needs some more integration tho
2021-08-16 start main board pcb
2021-08-16 Main board pcb rev1 done and ordered
2021-08-29 Fix error in schema
    burned 4 regulatorsy
2021-08-29 Rev2 of pcb that does not burn regulators
2021-08-30 Add ctrl sw
    found issue with leds on rj45
    might have problems with uart pins in rj45
2021-09-03 Rev 2 controller PCB
    Now uses correct rj45 footprint.
    Leds should work!
    Added 1 more mounting hole (H5)
2021-09-14 Controller code and update pmos
2021-09-15 refactoring and segment
2021-09-16 Now with working display and random shapes+colors
2021-10-03 7seg works on thing that is put together
2021-10-05 Add bodge board ....
    also controller is good
2021-10-06 Is wurkin!
    missing one DC DC conv and mounting on wall
2021-10-06 GOTTA GO FAAAST
2021-10-19 Update screen refresh to remove flashing
